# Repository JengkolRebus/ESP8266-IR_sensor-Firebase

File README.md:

# ESP8266-IR_sensor-Firebase
Kontrol relay dengan ESP8266 dengan sensor IR atau menggunakan aplikasi android melalui realtime database; Firebase.

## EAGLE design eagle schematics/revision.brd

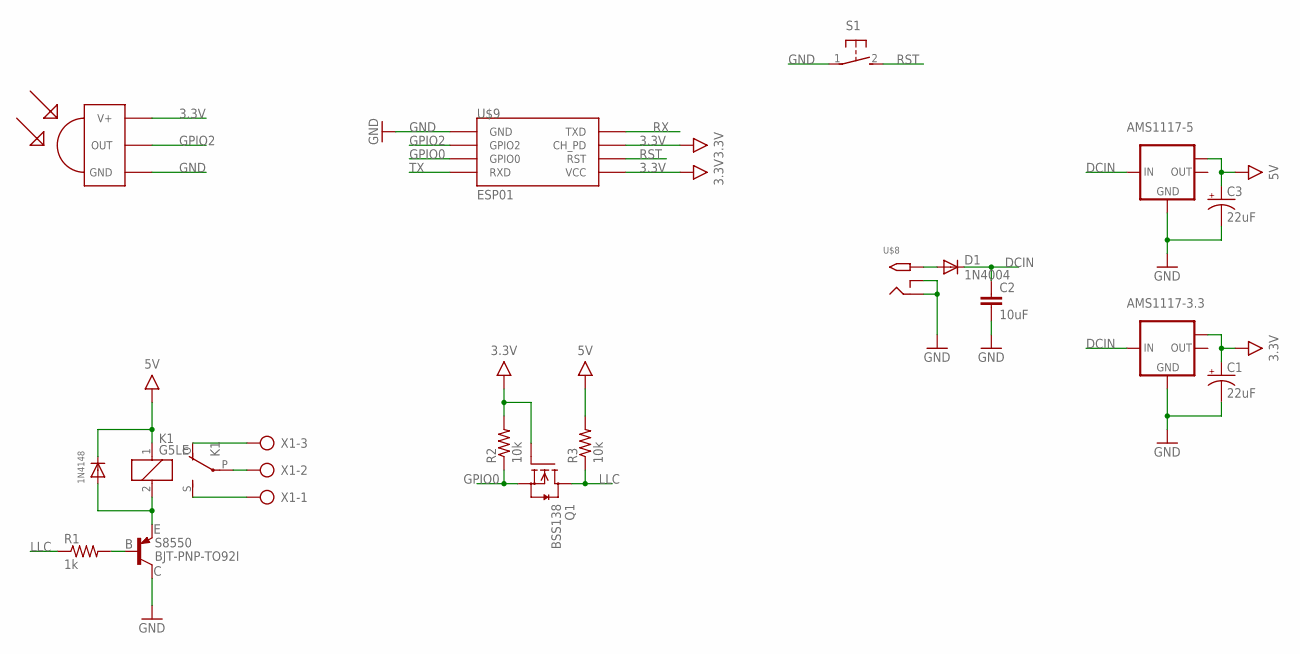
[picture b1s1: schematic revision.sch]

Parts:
1N4148: DIODESOD-123; SOD-123
AMS1117-3.3, AMS1117-5: LM1117MPX-3.3; SOT223
C1, C3: 22uF; EIA3216-KIT
C2: 10uF; 0805
D1: 1N4004; DO41-10
K1: G5LE
Q1: BSS138; SOT23
R1: 1k; 0805
R2, R3: 10k; 0805
S1: 31-XX; B3F-31XX
S8550: BJT-PNP-TO92I; TO92I
U$8: 2.1MMJACKTHM; PJ-102A
U$9: ESP01
U$10: TSOP1736; TSOP17XX
X1: AK300/3

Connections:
3.3V: AMS1117-3.3.TAB (OUT1), C1.A (+), Q1.1 (G), R2.2, U$9.CH_PD, U$9.VCC, U$10.V+
5V: 1N4148.C, AMS1117-5.TAB (OUT1), C3.A (+), K1.1, R3.2
DCIN: AMS1117-3.3.3 (IN), AMS1117-5.3 (IN), C2.1, D1.C
GND: AMS1117-3.3.1 (GND), AMS1117-5.1 (GND), C1.C (-), C2.2, C3.C (-), S1.1, S8550.C, U$8.RING, U$8.RING_SW, U$9.GND, U$10.GND
GPIO0: Q1.2 (S), R2.1, U$9.GPIO0
GPIO2: U$9.GPIO2, U$10.OUT
LLC: Q1.3 (D), R1.1, R3.1
unnamed: R1.2, S8550.B
unnamed: K1.O, X1.3
unnamed: K1.P, X1.2
unnamed: K1.S, X1.1
unnamed: D1.A, U$8.TIP
unnamed: 1N4148.A, K1.2, S8550.E
RST: S1.2 (S), U$9.RST
RX: U$9.TX (TXD)
TX: U$9.RX (RXD)

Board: 2 copper layers, 18 parts (1 on the bottom side), 14 nets, no tracks yet.

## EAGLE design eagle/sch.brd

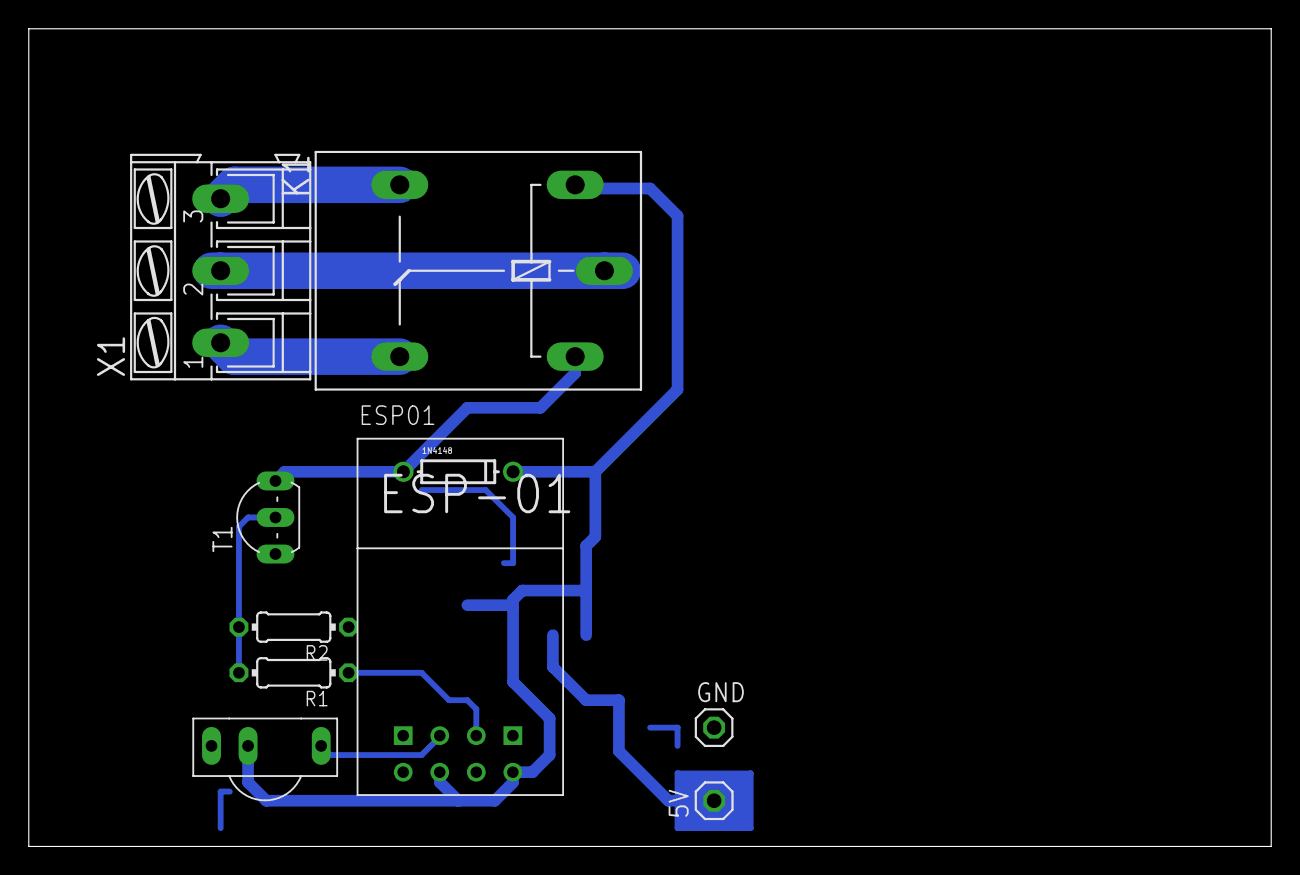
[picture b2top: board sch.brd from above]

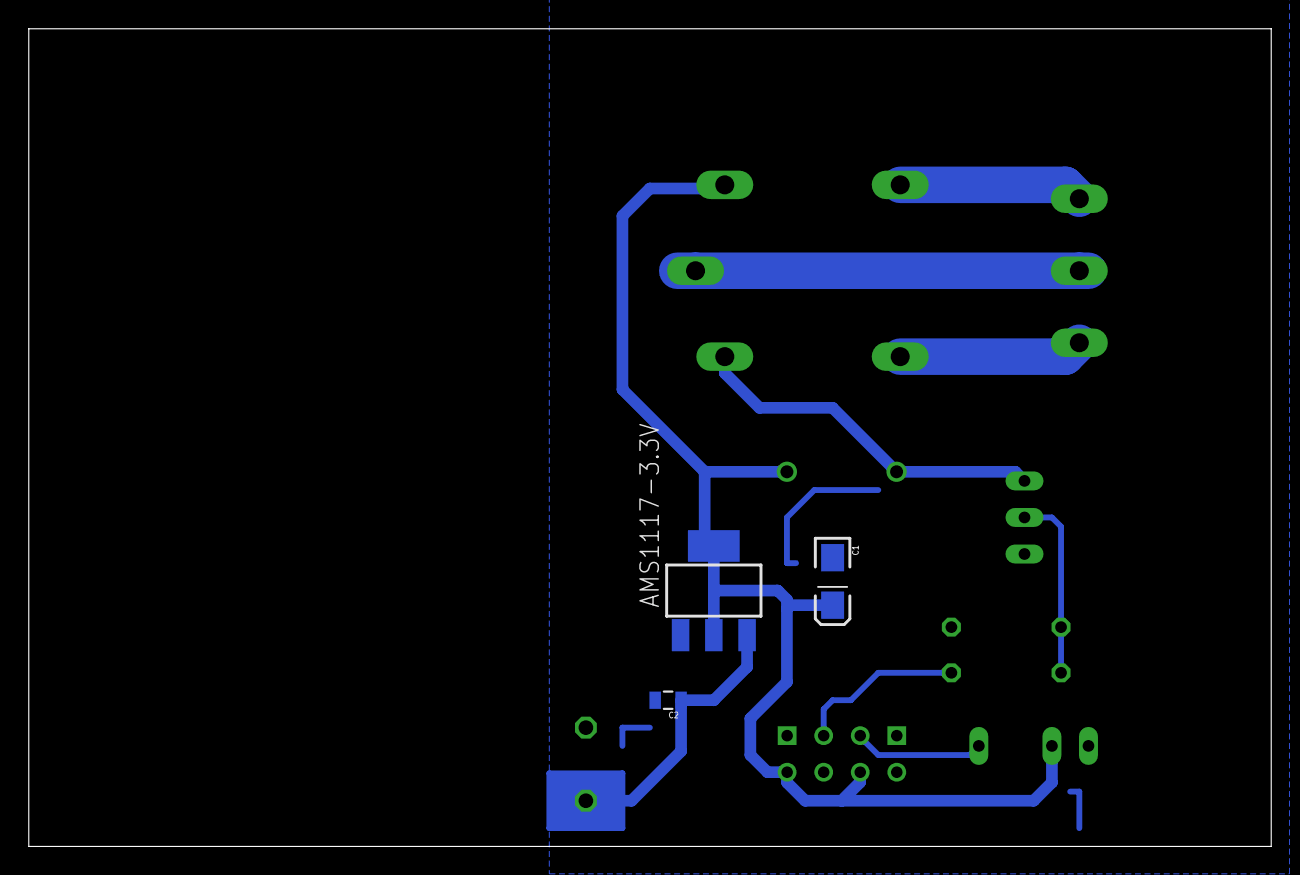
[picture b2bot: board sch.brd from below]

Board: 2 copper layers, 86.3 x 56.8 mm, 13 parts (3 on the bottom side), 10 nets.

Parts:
1N4148: DO-1N4148
5V: 1X01
AMS1117-3.3V: LM1117IMPX-3.3; SOT223
C1: 22uF; EIA3216-KIT
C2: 10uF; 0805
ESP01: ESP01
GND: 1X01
K1: G5LE
R1: 1k; 0204/7
R2: 10k; 0204/7
T1: 2N2222; TO92-EBC-OVAL
U$1: TSOP1736; TSOP17XX
X1: AK300/3

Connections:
3.3V: 1N4148.C, AMS1117-3.3V.2, AMS1117-3.3V.TAB, C1.A, ESP01.CH_PD, ESP01.VCC, K1.1, U$1.V+
5V: 5V.1, AMS1117-3.3V.3, C2.1
COM: K1.P, X1.2
GND: AMS1117-3.3V.1, C1.C, C2.2, ESP01.GND, GND.1, R2.1, T1.E, U$1.GND
GPIO0: ESP01.GPIO0, R1.1
GPIO2: ESP01.GPIO2, U$1.OUT
unnamed: R1.2, R2.2, T1.B
unnamed: 1N4148.A, K1.2, T1.C
NC: K1.O, X1.1
NO: K1.S, X1.3

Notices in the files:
parts and their libraries:
SparkFun-Passives: Licensing: Creative Commons ShareAlike 4.0 International - https://creativecommons.org/licenses/by-sa/4.0
m-pad-2.1: License : GNU General Public License version 2 (see bottom)
